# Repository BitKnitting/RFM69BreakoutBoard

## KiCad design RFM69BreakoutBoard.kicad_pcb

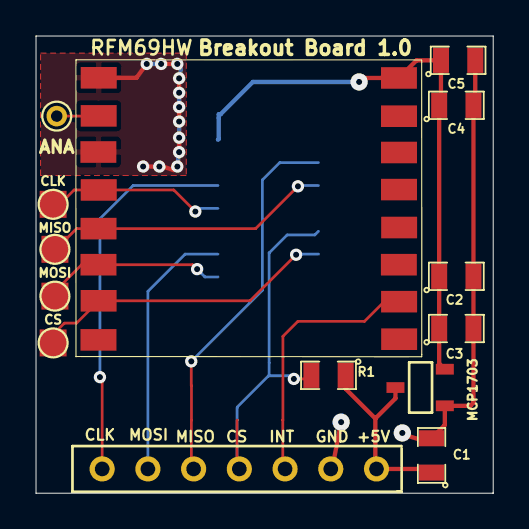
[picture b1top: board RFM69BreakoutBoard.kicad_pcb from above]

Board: 2 copper layers, 25.4 x 25.4 mm, 15 parts (1 on the bottom side), 13 nets.

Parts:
C1: 1u; SM0805
C2, C4: 10u; SM0805
C3, C5: .1u; SM0805
P1: BB Holes; 7_PINS
P8, P9, P10, P11, P12: TST; PINTST
R1: 10K; SM0805
U1: MCP1703; SOT-23A
U2: 74HCT123; so-14
U3: RFM69HW

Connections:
+3.3V: C2.1, C3.1, C4.1, C5.1, U1.2, U2.14, U3.8
+5V: C1.1, P1.1, R1.1, U1.3
/ANA: P12.1, U3.10
/CLK_3V3: P11.1, U2.11, U3.12
/CLK_5V: P1.7, U2.12
/CS_3V3: P8.1, U2.6, U3.15
/CS_5V: P1.4, R1.2, U2.5
/INT: P1.3, U3.2
/MISO_3V3: P10.1, U2.3, U3.13
/MISO_5V: P1.5, U2.2
/MOSI_3V3: P9.1, U2.8, U3.14
/MOSI_5V: P1.6, U2.9
GND: C1.2, C2.2, C3.2, C4.2, C5.2, P1.2, U1.1, U2.1, U2.4, U2.7, U2.10, U2.13, U3.9, U3.11

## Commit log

2014-02-22 first commit of RFM69HW Breakout Board schematic and PCBnew file to be loaded into kicad
2014-02-23 added BOM
2014-02-24 updated schematic after talking with Chris
2014-02-25 updated schema
2014-02-25 updated schema based on Sparkfun forum feedback
2014-02-26 added pdf of schmatic removed low res schematic.png
2014-02-26 added decoupling capacitors near RFM69, cleaned up GND
2014-02-26 removed png - low res
2014-02-26 edited antenna pin in schematic
2014-02-26 new pdf of schematic
2014-02-27 changed cap near rfm69hw to 47uF, modified ANA pin
2014-02-27 replaced larger caps to be electrolytic caps in the schematic
2014-02-27 updated schematic.pdf
2014-02-28 updated schema: changed 47uF cap to 10uF. Changed test point symbol
2014-02-28 problem with previous commit
2014-03-03 clean up
2014-03-03 updated the pdf of the schematic
2014-03-03 added BoM pdf
2014-03-03 started work on pcb layout
2014-03-03 update to test points. Changed electrolytic 10uF caps to ceramic
2014-03-04 updated BOM
2014-03-04 update to chip layout (PCBnew)
2014-03-07 removed 74LVC245 level shifter. Replaced with 74HCT125
2014-03-08 notice errors in schematic - updated schematic to fix
2014-03-09 first pass of trace
2014-03-09 updated schematic pdf
2014-03-10 changed test pins to pads, added a test pad for 5V
2014-03-12 2nd pass at PCB layout
2014-03-12 moved C1 to front copper on layout board
2014-03-13 added text to front and back silkscreen
2014-03-13 added via stitching to overlapping GND planes
2014-03-14 removed test points at connector
2014-03-14 adjusted space and spoke width around thermal relief pads in the GND plane
2014-03-17 updated PCB layout after correcting for freeDFM.com errors
